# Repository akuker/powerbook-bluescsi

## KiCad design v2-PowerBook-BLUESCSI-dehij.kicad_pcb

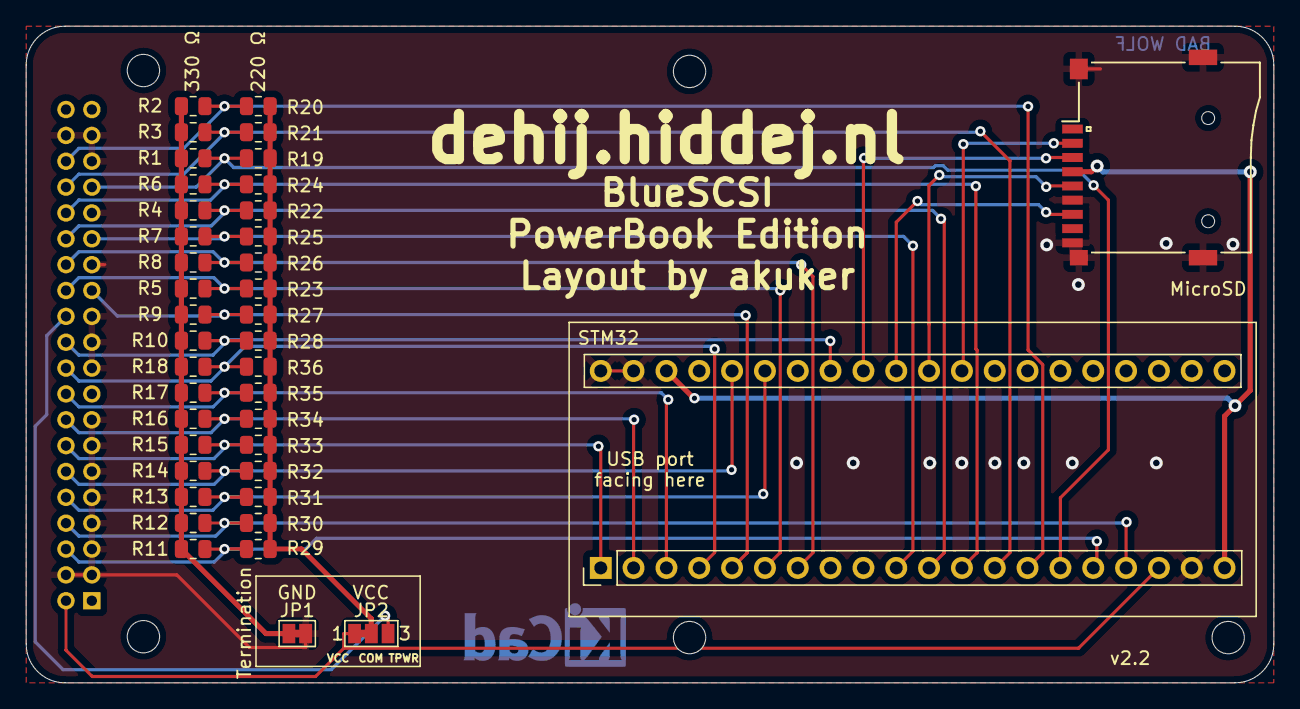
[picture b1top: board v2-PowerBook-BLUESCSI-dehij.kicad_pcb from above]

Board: 2 copper layers, 96.5 x 50.8 mm, 46 parts (1 on the bottom side), 28 nets.

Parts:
H1, H2, H3, H4, H5: MountingHole; MountingHole_2.5mm
J1: Micro_SD_Card; Conn_uSDcard
J2: Conn_02x20_Odd_Even; PinSocket_2x20_P2.00mm_Vertical
JP1: TERM_ENABLE_GND; SolderJumper-2_P1.3mm_Bridged_Pad1.0x1.5mm
JP2: TERM_VCC_ENABLE; SolderJumper-3_P1.3mm_Bridged12_Pad1.0x1.5mm_NumberLabels
R1, R2, R3, R4, R5, R6, R7, R8, R9, R10, R11, R12, R13, R14, R15, R16, R17, R18: 330; R_0805_2012Metric
R19, R20, R21, R22, R23, R24, R25, R26, R27, R28, R29, R30, R31, R32, R33, R34, R35, R36: 220; R_0805_2012Metric
U1: YAAJ_BluePill_Part_Like; YAAJ_BluePill_2

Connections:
+3V3: J1.4 (VDD), U1.20 (3V3), U1.38 (3V3)
/SCSI_ACK: J2.28, R8.2, R26.2, U1.7 (PA10)
/SCSI_ATN: J2.25, R9.2, R27.2, U1.5 (PA8)
/SCSI_BSY: J2.26, R5.2, R23.2, U1.6 (PA9)
/SCSI_CD: J2.34, R3.2, R21.2, U1.13 (PB5)
/SCSI_DAT0: J2.6, R11.2, R29.2, U1.16 (PB8)
/SCSI_DAT1: J2.8, R12.2, R30.2, U1.17 (PB9)
/SCSI_DAT2: J2.10, R13.2, R31.2, U1.35 (PB10)
/SCSI_DAT3: J2.12, R14.2, R32.2, U1.36 (PB11)
/SCSI_DAT4: J2.14, R15.2, R33.2, U1.1 (PB12)
/SCSI_DAT5: J2.16, R16.2, R34.2, U1.2 (PB13)
/SCSI_DAT6: J2.18, R17.2, R35.2, U1.3 (PB14)
/SCSI_DAT7: J2.20, R18.2, R36.2, U1.4 (PB15)
/SCSI_DBP: J2.22, R10.2, R28.2, U1.33 (PB0)
/SCSI_IO: J2.33, R1.2, R19.2, U1.15 (PB7)
/SCSI_MSG: J2.30, R4.2, R22.2, U1.11 (PB3)
/SCSI_REQ: J2.36, R2.2, R20.2, U1.14 (PB6)
/SCSI_RST: J2.29, R7.2, R25.2, U1.10 (PA15)
/SCSI_SEL: J2.32, R6.2, R24.2, U1.12 (PB4)
/SD_CLK: J1.5 (CLK), U1.30 (PA5)
/SD_CS: J1.2 (DAT3/CD), U1.29 (PA4)
/SD_MISO: J1.7 (DAT0), U1.31 (PA6)
/SD_MOSI: J1.3 (CMD), U1.32 (PA7)
/TERM_PWR: J2.24, JP2.3 (B)
GND: J1.6 (VSS), J1.9 (SHIELD), J2.3, J2.4, J2.5, J2.7, J2.9, J2.11, J2.13, J2.15, J2.19, J2.21, J2.23, J2.27, J2.31, J2.35, J2.37, J2.38, JP1.2, U1.19 (GND), U1.39 (GND), U1.40 (GND)
unnamed: JP1.1, R1.1, R2.1, R3.1, R4.1, R5.1, R6.1, R7.1, R8.1, R9.1, R10.1, R11.1, R12.1, R13.1, R14.1, R15.1, R16.1, R17.1, R18.1
unnamed: JP2.2 (C), R19.1, R20.1, R21.1, R22.1, R23.1, R24.1, R25.1, R26.1, R27.1, R28.1, R29.1, R30.1, R31.1, R32.1, R33.1, R34.1, R35.1, R36.1
VCC: J2.2, JP2.1 (A), U1.18 (5V)

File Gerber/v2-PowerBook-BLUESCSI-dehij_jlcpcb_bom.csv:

Comment,Designator,Footprint,LCSC
"MountingHole","H1,H2,H3,H4,H5","MountingHole:MountingHole_2.5mm",""
"Micro_SD_Card","J1","Other footprints:Conn_uSDcard","C164170"
"Conn_02x20_Odd_Even","J2","Connector_PinSocket_2.00mm:PinSocket_2x20_P2.00mm_Vertical",""
"TERM_ENABLE_GND","JP1","Jumper:SolderJumper-2_P1.3mm_Bridged_Pad1.0x1.5mm",""
"TERM_VCC_ENABLE","JP2","Jumper:SolderJumper-3_P1.3mm_Bridged12_Pad1.0x1.5mm_NumberLabels",""
"330","R1,R2,R3,R4,R5,R6,R7,R8,R9,R10,R11,R12,R13,R14,R15,R16,R17,R18","Resistor_SMD:R_0805_2012Metric","C365291"
"220","R19,R20,R21,R22,R23,R24,R25,R26,R27,R28,R29,R30,R31,R32,R33,R34,R35,R36","Resistor_SMD:R_0805_2012Metric","C163392"
"YAAJ_BluePill_Part_Like","U1","Footprints:YAAJ_BluePill_2",""

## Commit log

2022-09-08 Updated layout for JLCPCB assembly
